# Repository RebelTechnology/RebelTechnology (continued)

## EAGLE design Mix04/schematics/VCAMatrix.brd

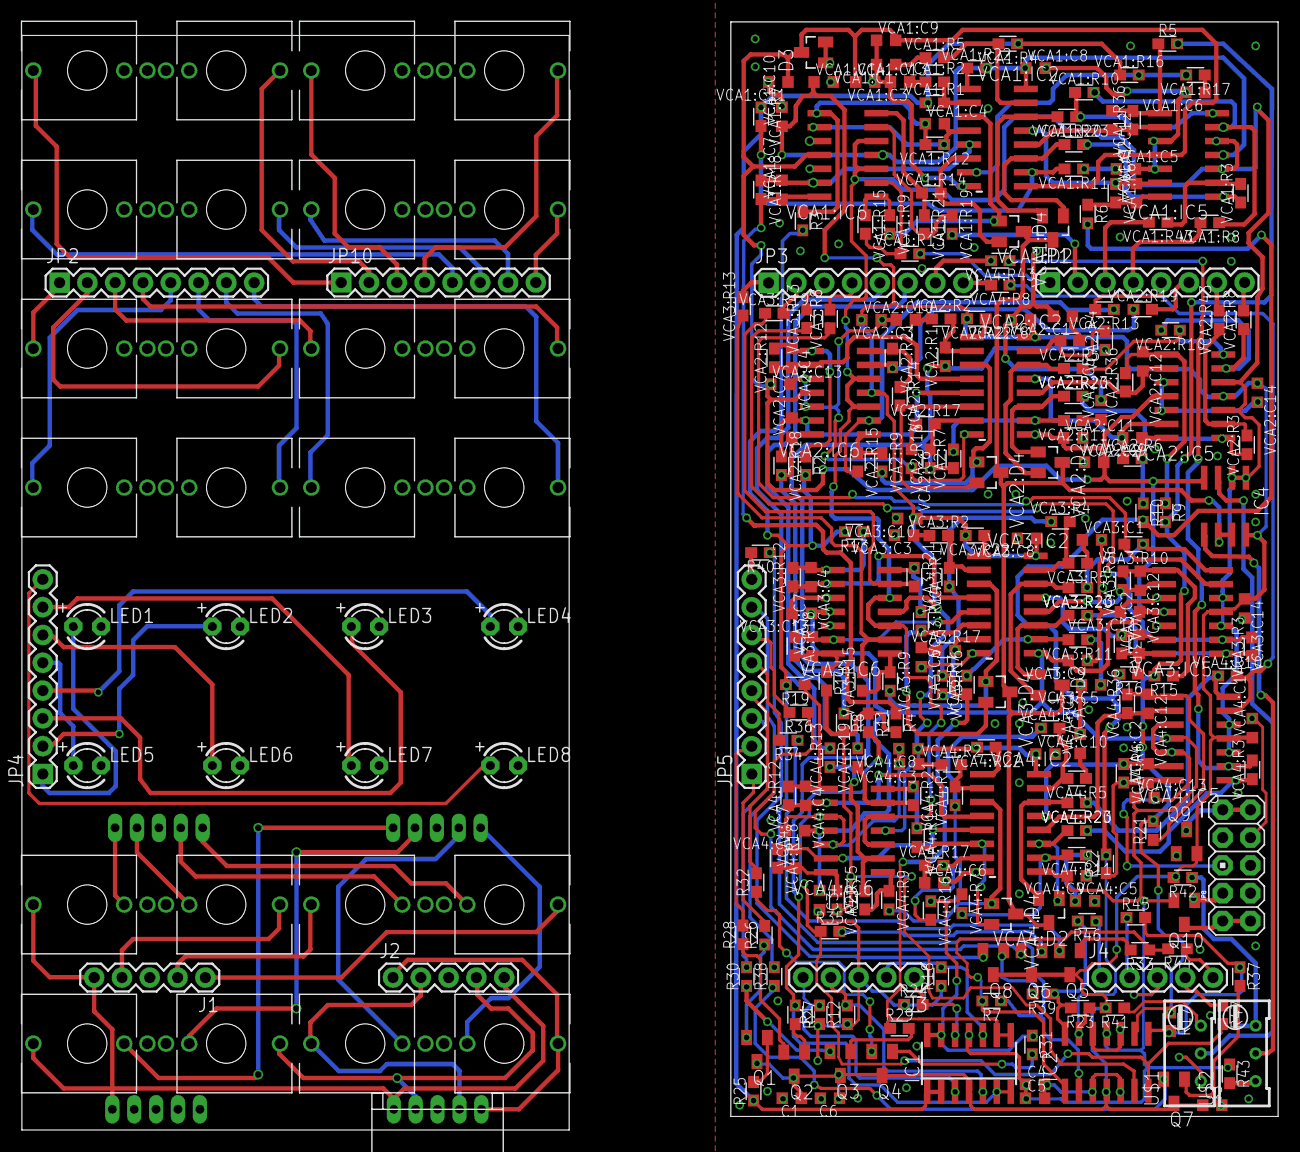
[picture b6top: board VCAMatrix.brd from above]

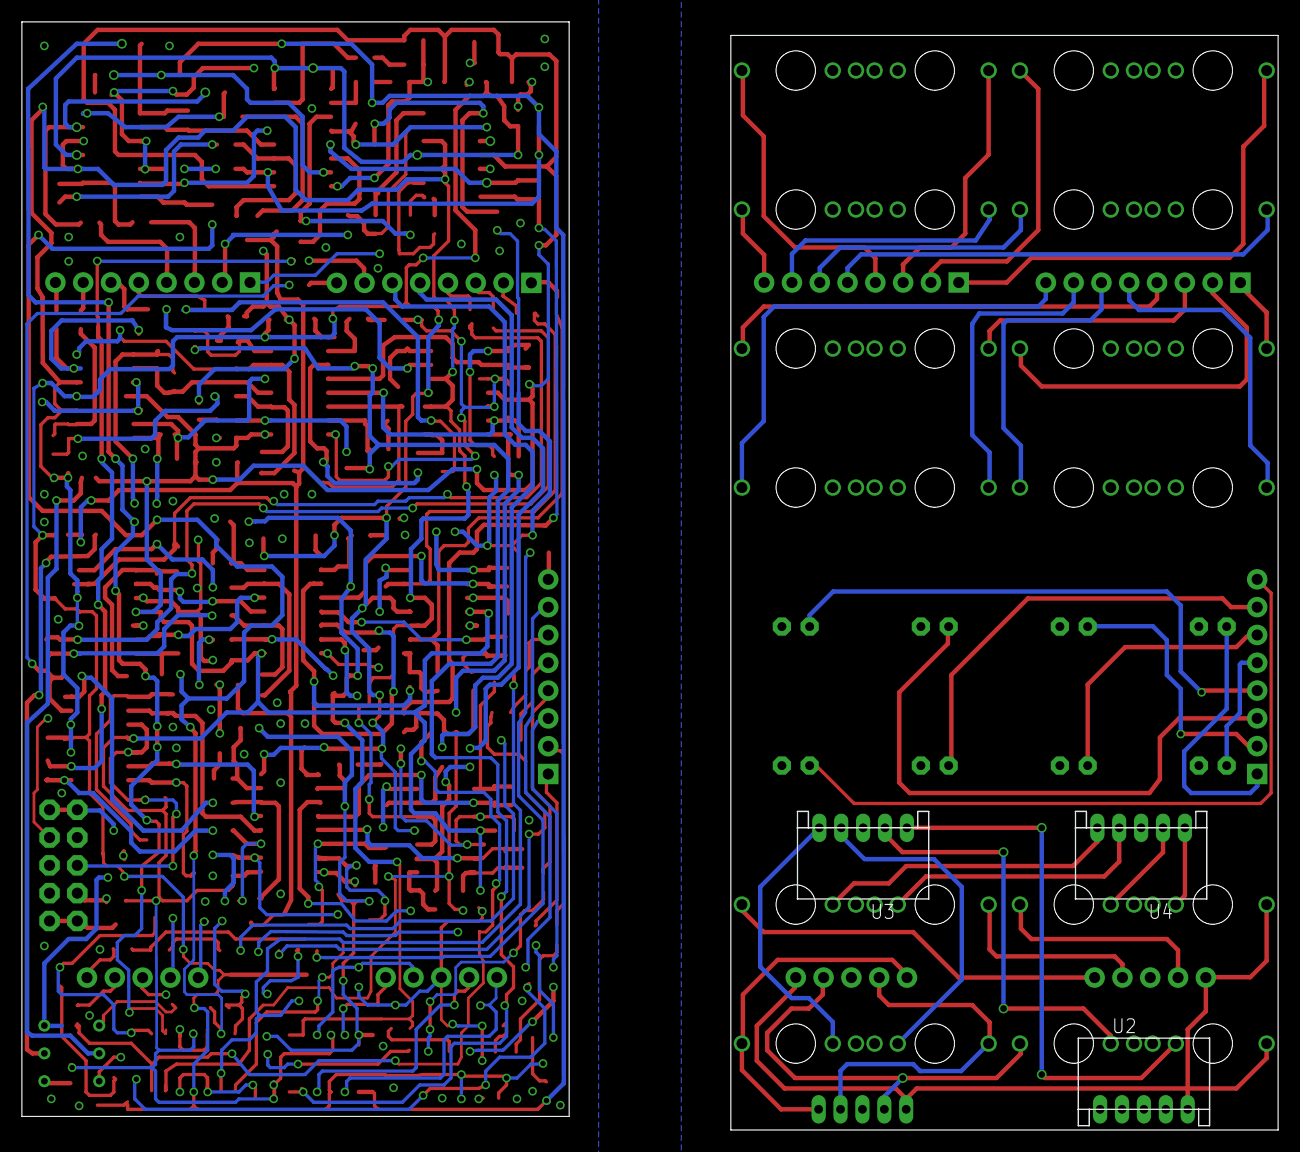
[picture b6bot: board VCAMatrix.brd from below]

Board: 2 copper layers, 50.0 x 100.0 mm, 292 parts (3 on the bottom side), 196 nets.

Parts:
C1, C2, C3, C4, C5, C6: 100n; C0603K
CV_AA: THONKICONN
CV_AB: THONKICONN
CV_AC: THONKICONN
CV_AD: THONKICONN
CV_BA: THONKICONN
CV_BB: THONKICONN
CV_BC: THONKICONN
CV_BD: THONKICONN
CV_CA: THONKICONN
CV_CB: THONKICONN
CV_CC: THONKICONN
CV_CD: THONKICONN
CV_DA: THONKICONN
CV_DB: THONKICONN
CV_DC: THONKICONN
CV_DD: THONKICONN
D3: BAT54A; SOT23
IC1: QUAD_OPAMPD; SO14
IC2: TL074D; SO14
IC4: TL072D; SO08
IN_A: THONKICONN
IN_B: THONKICONN
IN_C: THONKICONN
IN_D: THONKICONN
J1, J2, J3, J4: 1X05
JP1, JP2, JP3, JP4, JP5, JP10: 1X08
JP8: M05X2PTH; AVR_ICSP
LED1, LED2, LED3, LED4, LED5, LED6, LED7, LED8: LED3MM
OUTA: THONKICONN
OUTB: THONKICONN
OUTC: THONKICONN
OUTD: THONKICONN
Q1, Q2, Q3, Q4, Q5, Q6, Q7, Q8: BC846ALT1SMD; SOT23
Q9: BSS84; SOT23
Q10: BSS123; SOT23
R1, R2, R3, R4, R5, R6, R7, R8, R9, R10, R11, R12, R13, R14, R15, R16, R17, R18, R19, R20, R21, R22, R23, R24: 100k; 0603
R25, R27, R29, R31, R33, R35, R37, R39: 20k; 0603
R26, R28, R30, R32, R34, R36, R38, R40: 560; 0603
R41, R42, R43: 10k; 0603
R44, R45, R46, R47: 1k; 0603
U1, U2, U3, U4: CON-JST_PH_5W
U$1, U$2: RTRIM64W
VCA1:C1, VCA1:C3, VCA1:C5, VCA1:C6, VCA2:C1, VCA2:C3, VCA2:C5, VCA2:C6, VCA3:C1, VCA3:C3, VCA3:C5, VCA3:C6, VCA4:C1, VCA4:C3, VCA4:C5, VCA4:C6: 560p; C0603K
VCA1:C2, VCA1:C4, VCA1:C7, VCA1:C12, VCA2:C2, VCA2:C4, VCA2:C7, VCA2:C12, VCA3:C2, VCA3:C4, VCA3:C7, VCA3:C12, VCA4:C2, VCA4:C4, VCA4:C7, VCA4:C12: 100p; C0603K
VCA1:C8, VCA1:C9, VCA1:C10, VCA1:C11, VCA1:C13, VCA1:C14, VCA2:C8, VCA2:C9, VCA2:C10, VCA2:C11, VCA2:C13, VCA2:C14, VCA3:C8, VCA3:C9, VCA3:C10, VCA3:C11, VCA3:C13, VCA3:C14, VCA4:C8, VCA4:C9, VCA4:C10, VCA4:C11, VCA4:C13, VCA4:C14: 100n; C0603K
VCA1:D2, VCA1:D4, VCA2:D2, VCA2:D4, VCA3:D2, VCA3:D4, VCA4:D2, VCA4:D4: BAT54A; SOT23
VCA1:IC2, VCA2:IC2, VCA3:IC2, VCA4:IC2: SSM2164S; SOIC16N
VCA1:IC5, VCA1:IC6, VCA2:IC5, VCA2:IC6, VCA3:IC5, VCA3:IC6, VCA4:IC5, VCA4:IC6: TL074D; SO14
VCA1:R1, VCA1:R4, VCA1:R6, VCA1:R7, VCA1:R12, VCA1:R16, VCA1:R18, VCA1:R36, VCA2:R1, VCA2:R4, VCA2:R6, VCA2:R7, VCA2:R12, VCA2:R16, VCA2:R18, VCA2:R36, VCA3:R1, VCA3:R4, VCA3:R6, VCA3:R7, VCA3:R12, VCA3:R16, VCA3:R18, VCA3:R36, VCA4:R1, VCA4:R4, VCA4:R6, VCA4:R7, VCA4:R12, VCA4:R16, VCA4:R18, VCA4:R36: 30k; 0603
VCA1:R2, VCA1:R5, VCA1:R11, VCA1:R17, VCA2:R2, VCA2:R5, VCA2:R11, VCA2:R17, VCA3:R2, VCA3:R5, VCA3:R11, VCA3:R17, VCA4:R2, VCA4:R5, VCA4:R11, VCA4:R17: 500; 0603
VCA1:R3, VCA1:R10, VCA1:R15, VCA1:R21, VCA2:R3, VCA2:R10, VCA2:R15, VCA2:R21, VCA3:R3, VCA3:R10, VCA3:R15, VCA3:R21, VCA4:R3, VCA4:R10, VCA4:R15, VCA4:R21: 68k; 0603
VCA1:R8, VCA1:R13, VCA1:R19, VCA1:R43, VCA2:R8, VCA2:R13, VCA2:R19, VCA2:R43, VCA3:R8, VCA3:R13, VCA3:R19, VCA3:R43, VCA4:R8, VCA4:R13, VCA4:R19, VCA4:R43: 100k; 0603
VCA1:R9, VCA1:R14, VCA1:R20, VCA1:R23, VCA2:R9, VCA2:R14, VCA2:R20, VCA2:R23, VCA3:R9, VCA3:R14, VCA3:R20, VCA3:R23, VCA4:R9, VCA4:R14, VCA4:R20, VCA4:R23: 560; 0603
VCA1:R22, VCA2:R22, VCA3:R22, VCA4:R22: 6k; 0603

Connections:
+12V: C1.1, C2.1, C6.1, IC1.4, IC2.4, IC4.8, Q1.3, Q2.3, Q3.3, Q4.3, Q5.3, Q6.3, Q7.3, Q8.3, Q9.2, R41.2, R42.2, VCA1:C8.1, VCA1:C10.1, VCA1:C14.1, VCA1:IC2.16, VCA1:IC5.4, VCA1:IC6.4, VCA1:R22.2, VCA2:C8.1, VCA2:C10.1, VCA2:C14.1, VCA2:IC2.16, VCA2:IC5.4, VCA2:IC6.4, VCA2:R22.2, VCA3:C8.1, VCA3:C10.1, VCA3:C14.1, VCA3:IC2.16, VCA3:IC5.4, VCA3:IC6.4, VCA3:R22.2, VCA4:C8.1, VCA4:C10.1, VCA4:C14.1, VCA4:IC2.16, VCA4:IC5.4, VCA4:IC6.4, VCA4:R22.2
-12V: C3.1, C4.1, C5.1, D3.3, IC1.11, IC2.11, IC4.4, Q10.2, R43.1, VCA1:C9.2, VCA1:C11.1, VCA1:C13.1, VCA1:IC2.9, VCA1:IC5.11, VCA1:IC6.11, VCA2:C9.2, VCA2:C11.1, VCA2:C13.1, VCA2:IC2.9, VCA2:IC5.11, VCA2:IC6.11, VCA3:C9.2, VCA3:C11.1, VCA3:C13.1, VCA3:IC2.9, VCA3:IC5.11, VCA3:IC6.11, VCA4:C9.2, VCA4:C11.1, VCA4:C13.1, VCA4:IC2.9, VCA4:IC5.11, VCA4:IC6.11
CLAMP_REF: IC4.6, IC4.7, VCA1:D2.3, VCA1:D4.3, VCA2:D2.3, VCA2:D4.3, VCA3:D2.3, VCA3:D4.3, VCA4:D2.3, VCA4:D4.3
CV_AA: CV_AA.P$3, JP1.1, JP10.1, VCA1:R13.2
CV_AB: CV_AB.P$3, JP1.2, JP10.2, VCA1:R19.2
CV_AC: CV_AC.P$3, JP1.3, JP10.3, VCA1:R43.2
CV_AD: CV_AD.P$3, JP1.4, JP10.4, VCA1:R8.2
CV_BA: CV_BA.P$3, JP1.5, JP10.5, VCA2:R13.2
CV_BB: CV_BB.P$3, JP1.6, JP10.6, VCA2:R19.2
CV_BC: CV_BC.P$3, JP1.7, JP10.7, VCA2:R43.2
CV_BD: CV_BD.P$3, JP1.8, JP10.8, VCA2:R8.2
CV_CA: CV_CA.P$3, JP2.1, JP3.1, VCA3:R13.2
CV_CB: CV_CB.P$3, JP2.2, JP3.2, VCA3:R19.2
CV_CC: CV_CC.P$3, JP2.3, JP3.3, VCA3:R43.2
CV_CD: CV_CD.P$3, JP2.4, JP3.4, VCA3:R8.2
CV_DA: CV_DA.P$3, JP2.5, JP3.5, VCA4:R13.2
CV_DB: CV_DB.P$3, JP2.6, JP3.6, VCA4:R19.2
CV_DC: CV_DC.P$3, JP2.7, JP3.7, VCA4:R43.2
CV_DD: CV_DD.P$3, JP2.8, JP3.8, VCA4:R8.2
GND: C1.2, C2.2, C3.2, C4.2, C5.2, C6.2, CV_AA.P$1, CV_AA.P$2, CV_AB.P$1, CV_AB.P$2, CV_AC.P$1, CV_AC.P$2, CV_AD.P$1, CV_AD.P$2, CV_BA.P$1, CV_BA.P$2, CV_BB.P$1, CV_BB.P$2, CV_BC.P$1, CV_BC.P$2, CV_BD.P$1, CV_BD.P$2, CV_CA.P$1, CV_CA.P$2, CV_CB.P$1, CV_CB.P$2, CV_CC.P$1, CV_CC.P$2, CV_CD.P$1, CV_CD.P$2, CV_DA.P$1, CV_DA.P$2, CV_DB.P$1, CV_DB.P$2, CV_DC.P$1, CV_DC.P$2, CV_DD.P$1, CV_DD.P$2, D3.1, D3.2, IC2.3, IC2.5, IC2.10, IC2.12, IN_A.P$1, IN_B.P$1, IN_C.P$1, IN_D.P$1, J1.3, J2.3, J3.3, J4.3, JP8.3, JP8.4, JP8.5, JP8.6, JP8.7, JP8.8, LED1.K, LED2.K, LED3.K, LED4.K, LED5.K, LED6.K, LED7.K, LED8.K, OUTA.P$1, OUTB.P$1, OUTC.P$1, OUTD.P$1, Q9.1, Q10.1, R1.1, R12.1, R18.1, R24.1, U1.P3, U2.P3, U3.P3, U4.P3, U$1.1, VCA1:C1.2, VCA1:C3.2, VCA1:C5.2, VCA1:C6.2, VCA1:C8.2, VCA1:C9.1, VCA1:C10.2, VCA1:C11.2, VCA1:C13.2, VCA1:C14.2, VCA1:IC2.8, VCA1:IC5.10, VCA1:IC5.12, VCA1:IC6.10, VCA1:IC6.12, VCA2:C1.2, VCA2:C3.2, VCA2:C5.2, VCA2:C6.2, VCA2:C8.2, VCA2:C9.1, VCA2:C10.2, VCA2:C11.2, VCA2:C13.2, VCA2:C14.2, VCA2:IC2.8, VCA2:IC5.10, VCA2:IC5.12, VCA2:IC6.10, VCA2:IC6.12, VCA3:C1.2, VCA3:C3.2, VCA3:C5.2, VCA3:C6.2, VCA3:C8.2, VCA3:C9.1, VCA3:C10.2, VCA3:C11.2, VCA3:C13.2, VCA3:C14.2, VCA3:IC2.8, VCA3:IC5.10, VCA3:IC5.12, VCA3:IC6.10, VCA3:IC6.12, VCA4:C1.2, VCA4:C3.2, VCA4:C5.2, VCA4:C6.2, VCA4:C8.2, VCA4:C9.1, VCA4:C10.2, VCA4:C11.2, VCA4:C13.2, VCA4:C14.2, VCA4:IC2.8, VCA4:IC5.10, VCA4:IC5.12, VCA4:IC6.10, VCA4:IC6.12
IN_A: IC1.3, IN_A.P$3, J1.5, J3.5, R1.2, U2.P1
IN_B: IC1.5, IN_B.P$3, J1.4, J3.4, R12.2, U2.P2
IN_C: IC1.10, IN_C.P$3, J1.2, J3.2, R18.2, U2.P4
IN_D: IC1.12, IN_D.P$3, J1.1, J3.1, R24.2, U2.P5
LED_1: JP4.1, JP5.1, LED1.A, R26.2
LED_2: JP4.2, JP5.2, LED2.A, R28.2
LED_3: JP4.3, JP5.3, LED3.A, R30.2
LED_4: JP4.4, JP5.4, LED4.A, R32.2
LED_5: JP4.5, JP5.5, LED5.A, R34.2
LED_6: JP4.6, JP5.6, LED6.A, R36.2
LED_7: JP4.7, JP5.7, LED7.A, R38.2
LED_8: JP4.8, JP5.8, LED8.A, R40.2
unnamed: IC1.6, IC1.7, R27.1, VCA2:R1.1, VCA2:R4.1, VCA2:R7.1, VCA2:R16.1
unnamed: Q1.2, R26.1
unnamed: JP8.9, JP8.10, Q10.3
unnamed: R3.1, VCA1:C4.1, VCA1:IC6.8, VCA1:R12.2
unnamed: R4.1, VCA1:C7.1, VCA1:IC6.14, VCA1:R18.2
unnamed: R5.1, VCA1:C12.1, VCA1:IC5.8, VCA1:R36.2
unnamed: R6.1, VCA1:C2.1, VCA1:IC5.14, VCA1:R6.2
unnamed: IC2.9, R5.2, R9.2, R15.2, R17.1, R21.2
unnamed: R41.1, U$1.3
unnamed: R2.1, VCA2:C4.1, VCA2:IC6.8, VCA2:R12.2
unnamed: R8.1, VCA2:C7.1, VCA2:IC6.14, VCA2:R18.2
unnamed: R9.1, VCA2:C12.1, VCA2:IC5.8, VCA2:R36.2
unnamed: R10.1, VCA2:C2.1, VCA2:IC5.14, VCA2:R6.2
unnamed: Q1.1, R25.2
unnamed: IC1.13, IC1.14, R31.1, VCA4:R1.1, VCA4:R4.1, VCA4:R7.1, VCA4:R16.1
unnamed: IC1.8, IC1.9, R29.1, VCA3:R1.1, VCA3:R4.1, VCA3:R7.1, VCA3:R16.1
unnamed: Q8.2, R40.1
unnamed: R13.1, VCA3:C4.1, VCA3:IC6.8, VCA3:R12.2
unnamed: R14.1, VCA3:C7.1, VCA3:IC6.14, VCA3:R18.2
unnamed: R15.1, VCA3:C12.1, VCA3:IC5.8, VCA3:R36.2
unnamed: R16.1, VCA3:C2.1, VCA3:IC5.14, VCA3:R6.2
unnamed: IC4.3, U$1.2
unnamed: IC4.1, IC4.2, VCA1:IC5.3, VCA1:IC5.5, VCA1:IC6.3, VCA1:IC6.5, VCA2:IC5.3, VCA2:IC5.5, VCA2:IC6.3, VCA2:IC6.5, VCA3:IC5.3, VCA3:IC5.5, VCA3:IC6.3, VCA3:IC6.5, VCA4:IC5.3, VCA4:IC5.5, VCA4:IC6.3, VCA4:IC6.5
unnamed: R19.1, VCA4:C4.1, VCA4:IC6.8, VCA4:R12.2
unnamed: R20.1, VCA4:C7.1, VCA4:IC6.14, VCA4:R18.2
unnamed: R21.1, VCA4:C12.1, VCA4:IC5.8, VCA4:R36.2
unnamed: R22.1, VCA4:C2.1, VCA4:IC5.14, VCA4:R6.2
unnamed: R42.1, U$2.3
unnamed: Q6.1, R35.2
unnamed: Q2.1, R27.2
unnamed: IC2.13, R6.2, R10.2, R16.2, R22.2, R23.1
unnamed: Q2.2, R28.1
unnamed: Q3.1, R29.2
unnamed: Q3.2, R30.1
unnamed: Q6.2, R36.1
unnamed: OUTA.P$2, U3.P5
unnamed: Q4.1, R31.2
unnamed: IC2.2, R2.2, R3.2, R7.1, R13.2, R19.2
unnamed: IC2.6, R4.2, R8.2, R11.1, R14.2, R20.2
unnamed: Q4.2, R32.1
unnamed: Q7.1, R37.2
unnamed: Q5.1, R33.2
unnamed: Q5.2, R34.1
unnamed: Q7.2, R38.1
unnamed: Q8.1, R39.2
unnamed: IN_B.P$2, U4.P4
unnamed: IN_C.P$2, U4.P2
unnamed: IN_D.P$2, U4.P1
unnamed: OUTB.P$2, U3.P4
unnamed: OUTC.P$2, U3.P2
unnamed: OUTD.P$2, U3.P1
unnamed: IN_A.P$2, U4.P5
unnamed: R43.2, U$2.1
unnamed: IC4.5, U$2.2
unnamed: JP8.1, JP8.2, Q9.3
unnamed: IC1.1, IC1.2, R25.1, VCA1:R1.1, VCA1:R4.1, VCA1:R7.1, VCA1:R16.1
OUTPUT_A: IC2.1, R7.2, R33.1, R44.2
OUTPUT_B: IC2.7, R11.2, R35.1, R47.2
OUTPUT_C: IC2.8, R17.2, R37.1, R45.2
OUTPUT_D: IC2.14, R23.2, R39.1, R46.2
OUT_A: J2.5, J4.5, OUTA.P$3, R44.1, U1.P1
OUT_B: J2.4, J4.4, OUTB.P$3, R47.1, U1.P2
OUT_C: J2.2, J4.2, OUTC.P$3, R45.1, U1.P4
OUT_D: J2.1, J4.1, OUTD.P$3, R46.1, U1.P5
VCA1:IC2_1: VCA1:IC5.7, VCA1:R10.1, VCA1:R20.1
VCA1:IC2_2: VCA1:IC5.6, VCA1:R8.1, VCA1:R10.2
VCA1:IC2_3: VCA1:IC6.1, VCA1:R9.1, VCA1:R15.1
VCA1:IC2_4: VCA1:IC5.2, VCA1:R3.2, VCA1:R43.1
VCA1:IC2_5: VCA1:IC6.2, VCA1:R13.1, VCA1:R15.2
VCA1:IC2_6: VCA1:IC6.7, VCA1:R14.1, VCA1:R21.1
VCA1:IC2_7: VCA1:IC6.6, VCA1:R19.1, VCA1:R21.2
VCA1:IC2_11: VCA1:IC5.1, VCA1:R3.1, VCA1:R23.2
VCA1:N$1: VCA1:D4.1, VCA1:IC2.3, VCA1:R9.2
VCA1:N$2: VCA1:C1.1, VCA1:R5.1
VCA1:N$3: VCA1:C3.1, VCA1:R2.1
VCA1:N$4: VCA1:IC2.15, VCA1:R4.2, VCA1:R5.2
VCA1:N$5: VCA1:IC2.2, VCA1:R1.2, VCA1:R2.2
VCA1:N$6: VCA1:C2.2, VCA1:IC2.13, VCA1:IC5.13, VCA1:R6.1
VCA1:N$7: VCA1:D4.2, VCA1:IC2.6, VCA1:R14.2
VCA1:N$8: VCA1:D2.1, VCA1:IC2.11, VCA1:R23.1
VCA1:N$9: VCA1:C4.2, VCA1:IC2.4, VCA1:IC6.9, VCA1:R12.1
VCA1:N$11: VCA1:C6.1, VCA1:R17.1
VCA1:N$12: VCA1:IC2.7, VCA1:R16.2, VCA1:R17.2
VCA1:N$13: VCA1:C7.2, VCA1:IC2.5, VCA1:IC6.13, VCA1:R18.1
VCA1:N$14: VCA1:D2.2, VCA1:IC2.14, VCA1:R20.2
VCA1:N$17: VCA1:IC2.1, VCA1:R22.1
VCA1:N$19: VCA1:C5.1, VCA1:R11.1
VCA1:N$23: VCA1:IC2.10, VCA1:R7.2, VCA1:R11.2
VCA1:N$49: VCA1:C12.2, VCA1:IC2.12, VCA1:IC5.9, VCA1:R36.1
VCA2:IC2_1: VCA2:IC5.7, VCA2:R10.1, VCA2:R20.1
VCA2:IC2_2: VCA2:IC5.6, VCA2:R8.1, VCA2:R10.2
VCA2:IC2_3: VCA2:IC6.1, VCA2:R9.1, VCA2:R15.1
VCA2:IC2_4: VCA2:IC5.2, VCA2:R3.2, VCA2:R43.1
VCA2:IC2_5: VCA2:IC6.2, VCA2:R13.1, VCA2:R15.2
VCA2:IC2_6: VCA2:IC6.7, VCA2:R14.1, VCA2:R21.1
VCA2:IC2_7: VCA2:IC6.6, VCA2:R19.1, VCA2:R21.2
VCA2:IC2_11: VCA2:IC5.1, VCA2:R3.1, VCA2:R23.2
VCA2:N$1: VCA2:D4.1, VCA2:IC2.3, VCA2:R9.2
VCA2:N$2: VCA2:C1.1, VCA2:R5.1
VCA2:N$3: VCA2:C3.1, VCA2:R2.1
VCA2:N$4: VCA2:IC2.15, VCA2:R4.2, VCA2:R5.2
VCA2:N$5: VCA2:IC2.2, VCA2:R1.2, VCA2:R2.2
VCA2:N$6: VCA2:C2.2, VCA2:IC2.13, VCA2:IC5.13, VCA2:R6.1
VCA2:N$7: VCA2:D4.2, VCA2:IC2.6, VCA2:R14.2
VCA2:N$8: VCA2:D2.1, VCA2:IC2.11, VCA2:R23.1
VCA2:N$9: VCA2:C4.2, VCA2:IC2.4, VCA2:IC6.9, VCA2:R12.1
VCA2:N$11: VCA2:C6.1, VCA2:R17.1
VCA2:N$12: VCA2:IC2.7, VCA2:R16.2, VCA2:R17.2
VCA2:N$13: VCA2:C7.2, VCA2:IC2.5, VCA2:IC6.13, VCA2:R18.1
VCA2:N$14: VCA2:D2.2, VCA2:IC2.14, VCA2:R20.2
VCA2:N$17: VCA2:IC2.1, VCA2:R22.1
VCA2:N$19: VCA2:C5.1, VCA2:R11.1
VCA2:N$23: VCA2:IC2.10, VCA2:R7.2, VCA2:R11.2
VCA2:N$49: VCA2:C12.2, VCA2:IC2.12, VCA2:IC5.9, VCA2:R36.1
VCA3:IC2_1: VCA3:IC5.7, VCA3:R10.1, VCA3:R20.1
VCA3:IC2_2: VCA3:IC5.6, VCA3:R8.1, VCA3:R10.2
VCA3:IC2_3: VCA3:IC6.1, VCA3:R9.1, VCA3:R15.1
VCA3:IC2_4: VCA3:IC5.2, VCA3:R3.2, VCA3:R43.1
VCA3:IC2_5: VCA3:IC6.2, VCA3:R13.1, VCA3:R15.2
VCA3:IC2_6: VCA3:IC6.7, VCA3:R14.1, VCA3:R21.1
VCA3:IC2_7: VCA3:IC6.6, VCA3:R19.1, VCA3:R21.2
VCA3:IC2_11: VCA3:IC5.1, VCA3:R3.1, VCA3:R23.2
VCA3:N$1: VCA3:D4.1, VCA3:IC2.3, VCA3:R9.2
VCA3:N$2: VCA3:C1.1, VCA3:R5.1
VCA3:N$3: VCA3:C3.1, VCA3:R2.1
VCA3:N$4: VCA3:IC2.15, VCA3:R4.2, VCA3:R5.2
VCA3:N$5: VCA3:IC2.2, VCA3:R1.2, VCA3:R2.2
VCA3:N$6: VCA3:C2.2, VCA3:IC2.13, VCA3:IC5.13, VCA3:R6.1
VCA3:N$7: VCA3:D4.2, VCA3:IC2.6, VCA3:R14.2
VCA3:N$8: VCA3:D2.1, VCA3:IC2.11, VCA3:R23.1
VCA3:N$9: VCA3:C4.2, VCA3:IC2.4, VCA3:IC6.9, VCA3:R12.1
VCA3:N$11: VCA3:C6.1, VCA3:R17.1
VCA3:N$12: VCA3:IC2.7, VCA3:R16.2, VCA3:R17.2
VCA3:N$13: VCA3:C7.2, VCA3:IC2.5, VCA3:IC6.13, VCA3:R18.1
VCA3:N$14: VCA3:D2.2, VCA3:IC2.14, VCA3:R20.2
VCA3:N$17: VCA3:IC2.1, VCA3:R22.1
VCA3:N$19: VCA3:C5.1, VCA3:R11.1
VCA3:N$23: VCA3:IC2.10, VCA3:R7.2, VCA3:R11.2
VCA3:N$49: VCA3:C12.2, VCA3:IC2.12, VCA3:IC5.9, VCA3:R36.1
VCA4:IC2_1: VCA4:IC5.7, VCA4:R10.1, VCA4:R20.1
VCA4:IC2_2: VCA4:IC5.6, VCA4:R8.1, VCA4:R10.2
VCA4:IC2_3: VCA4:IC6.1, VCA4:R9.1, VCA4:R15.1
VCA4:IC2_4: VCA4:IC5.2, VCA4:R3.2, VCA4:R43.1
VCA4:IC2_5: VCA4:IC6.2, VCA4:R13.1, VCA4:R15.2
VCA4:IC2_6: VCA4:IC6.7, VCA4:R14.1, VCA4:R21.1
VCA4:IC2_7: VCA4:IC6.6, VCA4:R19.1, VCA4:R21.2
VCA4:IC2_11: VCA4:IC5.1, VCA4:R3.1, VCA4:R23.2
VCA4:N$1: VCA4:D4.1, VCA4:IC2.3, VCA4:R9.2
VCA4:N$2: VCA4:C1.1, VCA4:R5.1
VCA4:N$3: VCA4:C3.1, VCA4:R2.1
VCA4:N$4: VCA4:IC2.15, VCA4:R4.2, VCA4:R5.2
VCA4:N$5: VCA4:IC2.2, VCA4:R1.2, VCA4:R2.2
VCA4:N$6: VCA4:C2.2, VCA4:IC2.13, VCA4:IC5.13, VCA4:R6.1
VCA4:N$7: VCA4:D4.2, VCA4:IC2.6, VCA4:R14.2
VCA4:N$8: VCA4:D2.1, VCA4:IC2.11, VCA4:R23.1
VCA4:N$9: VCA4:C4.2, VCA4:IC2.4, VCA4:IC6.9, VCA4:R12.1
VCA4:N$11: VCA4:C6.1, VCA4:R17.1
VCA4:N$12: VCA4:IC2.7, VCA4:R16.2, VCA4:R17.2
VCA4:N$13: VCA4:C7.2, VCA4:IC2.5, VCA4:IC6.13, VCA4:R18.1
VCA4:N$14: VCA4:D2.2, VCA4:IC2.14, VCA4:R20.2
VCA4:N$17: VCA4:IC2.1, VCA4:R22.1
VCA4:N$19: VCA4:C5.1, VCA4:R11.1
VCA4:N$23: VCA4:IC2.10, VCA4:R7.2, VCA4:R11.2
VCA4:N$49: VCA4:C12.2, VCA4:IC2.12, VCA4:IC5.9, VCA4:R36.1

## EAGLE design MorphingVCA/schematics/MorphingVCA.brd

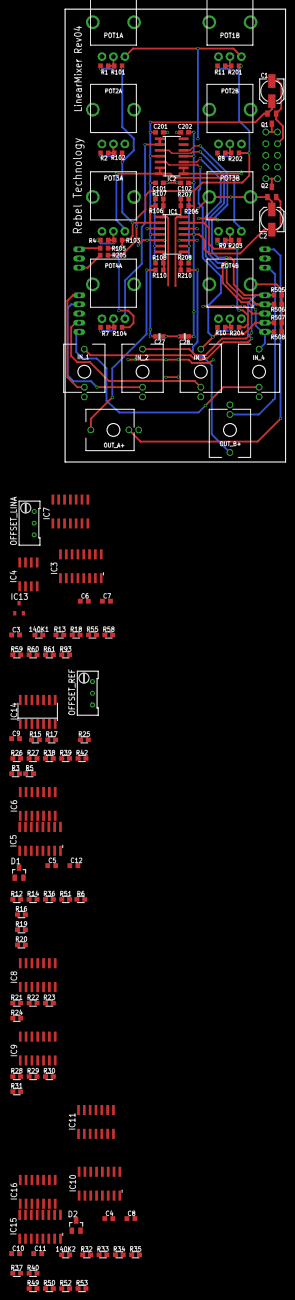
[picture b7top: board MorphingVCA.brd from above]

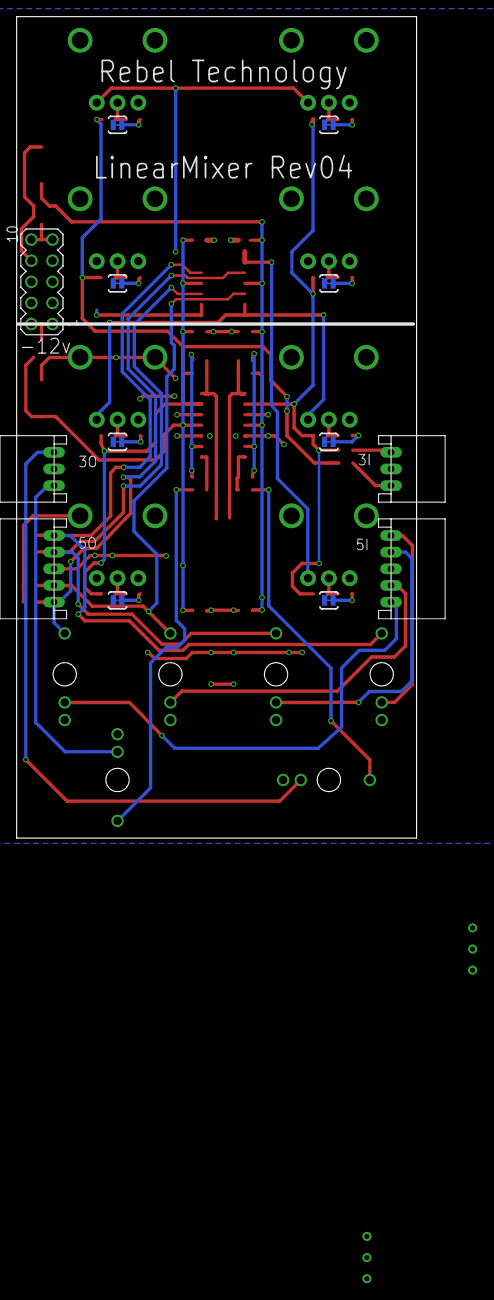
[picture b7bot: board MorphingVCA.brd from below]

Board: 2 copper layers, 48.1 x 98.7 mm, 142 parts (13 on the bottom side), 99 nets.

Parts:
3I, 3O: CON-JST_PH_3W
5I, 5O: CON-JST_PH_5W
140K1, 140K2: 100k; 0603
C1, C2: 10u; 153CLV-0505
C3, C9: 4u7; C0603K
C4, C6, C11, C12: 100p; C0603K
C5, C7, C8, C10: 560p; C0603K
C27, C28, C101, C102, C201, C202: 100n; C0603
D1, D2: BAT54A; SOT23
IC1, IC2, IC14: QUAD_OPAMPD; SO14
IC3, IC5, IC10, IC15: SSM2164S; SOIC16N
IC4: TL072D; SO08
IC6, IC7, IC8, IC9, IC11, IC16: TL074D; SO14
IC13: LM4041C12DBZ; DBZ_R-PDSO-G3
IN_1, IN_2, IN_3, IN_4: THONKICONN
OFFSET_LINA: RTRIM64W
OFFSET_REF: RTRIM64W
OUT_A+: THONKICONN
OUT_B+: THONKICONN
POT1A, POT1B, POT2A, POT2B, POT3A, POT3B, POT4A, POT4B: POT-ALPS-RK09L1140
Q1: SI2309CDS; SOT23
Q2: BSS123; SOT23
R1, R2, R4, R7, R8, R9, R10, R11: 2k7; R0603
R3, R13, R14, R16, R17, R20, R21, R22, R24, R25, R28, R29, R31: 10k; 0603
R5, R15, R18, R26, R27, R32, R33, R37, R38, R39, R40, R42, R55, R58, R61: 100k; 0603
R6, R30, R34, R36, R49, R52, R59: 30k; 0603
R12, R35, R50, R60: 500; 0603
R19: 5k1; 0603
R23: 20k; 0603
R51, R53: 560; 0603
R93: 510; 0603
R101, R102, R103, R104, R106, R108, R201, R202, R203, R204, R206, R208: 10k; R0603
R105, R205: 18k; R0603
R107, R207: 5k1; R0603
R110, R210: 1k; R0603
R505, R506, R507, R508: 1M; R0603
SJ1, SJ2, SJ3, SJ4, SJ5, SJ6, SJ7, SJ8: SOLDERJUMPERTRACE; SJ_2S-TRACE
SV1: MA05-2

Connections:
+12V: C1.+, C27.1, C101.1, C201.1, IC1.4, IC2.4, Q1.2, R93.2
-10V1: 140K1.2, R59.1, R61.1
-10V2: 140K2.2, R34.1, R37.1
-12V: C2.-, C28.1, C102.1, C202.1, IC1.11, IC2.11, Q2.2
CLAMP_REF: D1.3, D2.3
CV_SUM+_A: IC14.7, R38.1, R51.2
GND: 3I.P2, 3O.P2, 5I.P3, 5O.P3, 140K1.1, 140K2.1, C1.-, C2.+, C3.2, C5.2, C7.2, C8.2, C9.2, C10.2, C27.2, C28.2, C101.2, C102.2, C201.2, C202.2, IC1.3, IC1.5, IC1.10, IC1.12, IC3.8, IC5.8, IC6.10, IC7.5, IC10.8, IC11.5, IC13.2, IC14.3, IC14.12, IC15.8, IC16.10, IN_1.P$1, IN_2.P$1, IN_3.P$1, IN_4.P$1, OFFSET_LINA.1, OFFSET_REF.1, OUT_A+.P$1, OUT_B+.P$1, POT1A.1, POT1A.P$5, POT1A.P$6, POT1B.1, POT1B.P$5, POT1B.P$6, POT2A.1, POT2A.P$5, POT2A.P$6, POT2B.1, POT2B.P$5, POT2B.P$6, POT3A.1, POT3A.P$5, POT3A.P$6, POT3B.1, POT3B.P$5, POT3B.P$6, POT4A.1, POT4A.P$5, POT4A.P$6, POT4B.1, POT4B.P$5, POT4B.P$6, Q1.1, Q2.1, R14.2, R21.2, R27.2, R31.1, R505.2, R506.2, R507.2, R508.2, SJ1.1, SJ2.1, SJ3.1, SJ4.1, SJ5.1, SJ6.1, SJ7.1, SJ8.1, SV1.3, SV1.4, SV1.5, SV1.6, SV1.7, SV1.8
IC2C_1: D2.2, IC15.11, R53.1
IC2C_11: D1.2, IC5.11, R51.1
IC2_1: C4.2, IC10.13, IC11.13, R33.1
IC2_8: IC14.6, R5.1, R15.1, R38.2
IC2_13: C6.2, IC3.13, IC7.13, R58.1
IN_1: 5O.P1, IC2.12, IN_1.P$3, R505.1
IN_2: 5O.P2, IC2.10, IN_2.P$3, R506.1
IN_3: 5O.P4, IC2.5, IN_3.P$3, R507.1
IN_4: 5O.P5, IC2.3, IN_4.P$3, R508.1
IN_A: 3I.P3, R105.2
IN_A1: IC2.1, IC2.2, R16.1
IN_A2: IC2.6, IC2.7, R20.1, R22.1
IN_B: 3I.P1, R205.2
IN_B1: IC2.8, IC2.9
IN_B2: IC2.13, IC2.14
IN_SW_1: 5I.P5, IN_1.P$2
IN_SW_2: 5I.P4, IN_2.P$2
IN_SW_3: 5I.P2, IN_3.P$2
IN_SW_4: 5I.P1, IN_4.P$2
LIN+_OUT_A: C4.1, C6.1, IC3.14, IC7.14, IC10.14, IC11.14, R26.2, R53.2
LIN_POS_A: R32.1, R55.1
unnamed: Q2.3, SV1.1, SV1.2
unnamed: IC7.7, R18.2, R58.2
unnamed: IC7.6, R18.1, R55.2
unnamed: OFFSET_LINA.3, R13.1
unnamed: IC1.8, R208.2, R210.1
unnamed: IC1.7, R108.2, R110.1
unnamed: IC1.13, R201.1, R202.1, R203.1, R204.1, R205.1, R206.1
unnamed: C3.1, IC4.5, OFFSET_LINA.2
unnamed: OUT_A+.P$3, R110.2
unnamed: IC1.14, R206.2, R207.1
unnamed: IC1.2, R101.1, R102.1, R103.1, R104.1, R105.1, R106.1
unnamed: IC14.2, R39.2, R42.1
unnamed: IC1.1, R106.2, R107.1
unnamed: Q1.3, SV1.9, SV1.10
unnamed: OUT_B+.P$3, R210.2
unnamed: IC14.1, R15.2, R39.1
unnamed: R1.2, SJ1.2
unnamed: IC1.6, R107.2, R108.1
unnamed: OFFSET_REF.3, R3.1
unnamed: POT1B.2, R11.1, R201.2
unnamed: IC14.13, R17.1, R25.2
unnamed: R2.2, SJ2.2
unnamed: IC1.9, R207.2, R208.1
unnamed: R4.2, SJ3.2
unnamed: R7.2, SJ4.2
unnamed: R11.2, SJ5.2
unnamed: IC8.2, R23.1, R24.2
unnamed: R8.2, SJ6.2
unnamed: POT1A.2, R1.1, R101.2
unnamed: POT2B.2, R8.1, R202.2
unnamed: POT3B.2, R9.1, R203.2
unnamed: R9.2, SJ7.2
unnamed: R10.2, SJ8.2
unnamed: POT1A.3, POT1B.3
unnamed: IC8.3, R21.1, R22.2
unnamed: POT2A.3, POT2B.3
unnamed: POT3A.3, POT3B.3
unnamed: POT4A.3, POT4B.3
unnamed: IC14.5, R26.1, R27.1
unnamed: C9.1, OFFSET_REF.2, R17.2
unnamed: C5.1, R12.1
unnamed: IC5.10, R6.2, R12.2
unnamed: C12.2, IC5.12, IC6.9, R36.1
unnamed: POT4B.2, R10.1, R204.2
unnamed: IC9.2, R30.1, R31.2
unnamed: IC6.2, R19.1, R20.2
unnamed: POT4A.2, R7.1, R104.2
unnamed: IC6.3, R14.1, R16.2
unnamed: POT3A.2, R4.1, R103.2
unnamed: IC11.7, R33.2, R40.2
unnamed: POT2A.2, R2.1, R102.2
unnamed: IC9.3, R28.1, R29.2
unnamed: C7.1, R60.1
unnamed: IC3.15, R59.2, R60.2
unnamed: C8.1, R35.1
unnamed: IC10.15, R34.2, R35.2
unnamed: IC11.6, R32.2, R40.1
unnamed: C10.1, R50.1
unnamed: IC15.10, R49.2, R50.2
unnamed: C11.2, IC15.12, IC16.9, R52.1
OFFSET_LIN: IC4.6, IC4.7, IC7.12, IC11.12
OFFSET_REF: IC14.14, R5.2, R25.1
OUT_A1: IC8.1, R23.2
OUT_A2: IC9.1, R30.2
OUT_SW_A: 3O.P1, OUT_A+.P$2
OUT_SW_B: 3O.P3, OUT_B+.P$2
V+: IC3.16, IC4.8, IC5.16, IC6.4, IC7.4, IC8.4, IC9.4, IC10.16, IC11.4, IC14.4, IC15.16, IC16.4
V-: IC3.9, IC4.4, IC5.9, IC6.11, IC7.11, IC8.11, IC9.11, IC10.9, IC11.11, IC14.11, IC15.9, IC16.11
VCA_IN: IC6.1, R6.1, R19.2, R49.1
VCA_OUT: C11.1, C12.1, IC6.8, IC16.8, R24.1, R28.2, R36.2, R52.2
V_REF: IC13.1, R3.2, R13.2, R37.2, R61.2, R93.1
